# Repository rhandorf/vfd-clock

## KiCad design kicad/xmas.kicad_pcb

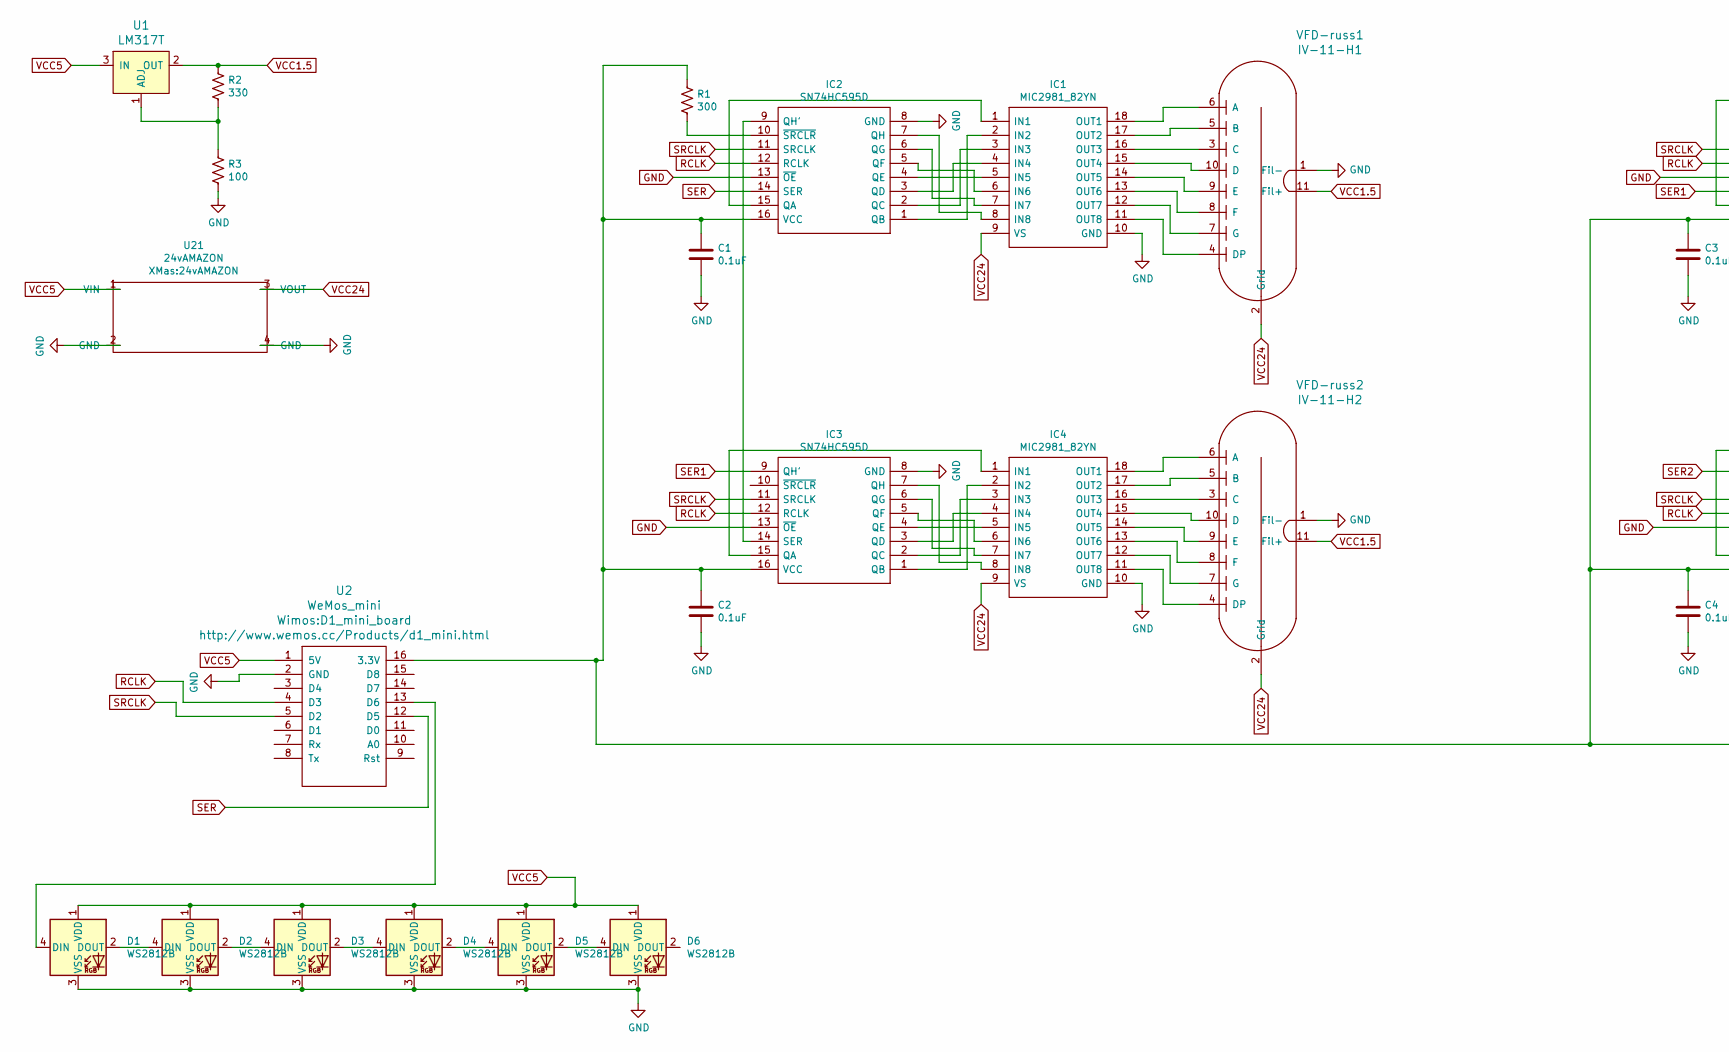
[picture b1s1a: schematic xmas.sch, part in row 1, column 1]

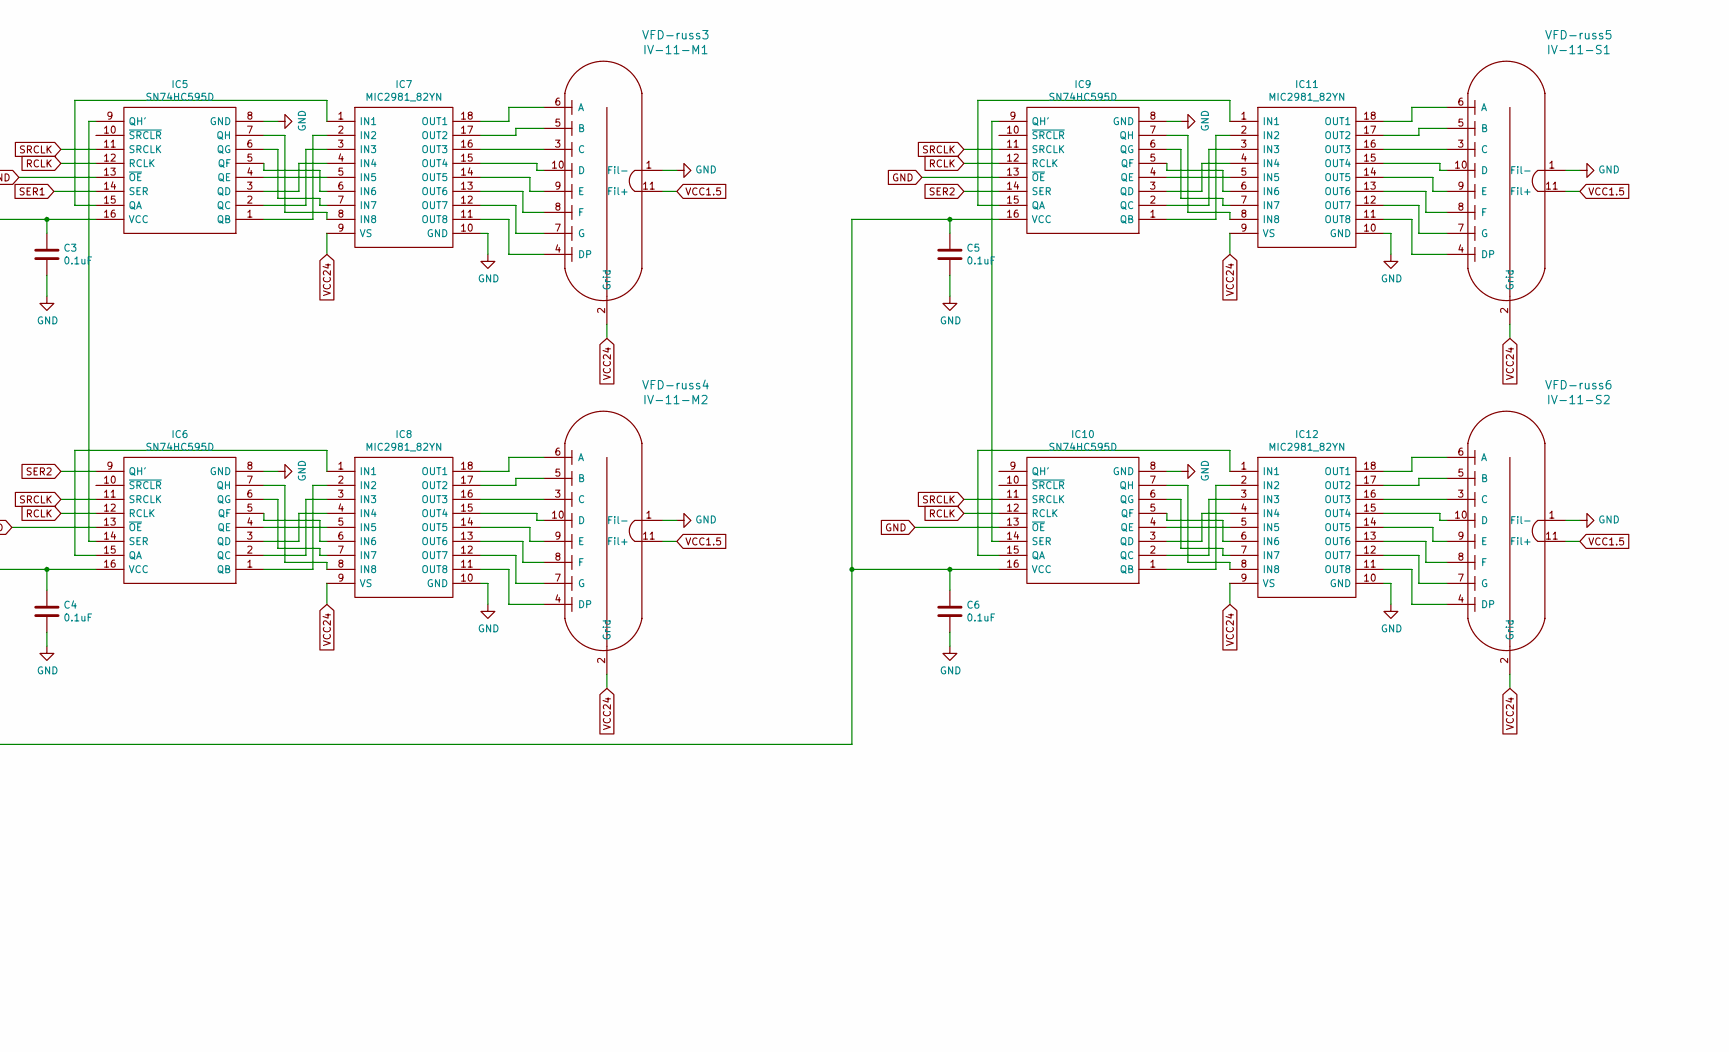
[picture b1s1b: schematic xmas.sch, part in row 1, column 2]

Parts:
C1, C2, C3, C4, C5, C6: 0.1uF; C_1206_3216Metric_Pad1.42x1.75mm_HandSolder
D1, D2, D3, D4, D5, D6: WS2812B; LED_WS2812B_PLCC4_5.0x5.0mm_P3.2mm
IC1, IC4, IC7, IC8, IC11, IC12: MIC2981_82YN; DIP773W53P254L2337H394Q18N; Mouser Part Number 998-MIC2981/82YN
IC2, IC3, IC5, IC6, IC9, IC10: SN74HC595D; SOIC127P600X175-16N; Mouser Part Number 595-SN74HC595D
R1: 300; R_1206_3216Metric_Pad1.42x1.75mm_HandSolder
R2: 330; R_1206_3216Metric_Pad1.42x1.75mm_HandSolder
R3: 100; R_1206_3216Metric_Pad1.42x1.75mm_HandSolder
U1: LM317T; TO-220-3; MPN LM317T; Digi-Key_PN 497-1575-5-ND
U2: WeMos_mini; D1_mini_board
U21: 24vAMAZON
VFD-russ1: IV-11-H1; IV-11
VFD-russ2: IV-11-H2; IV-11
VFD-russ3: IV-11-M1; IV-11
VFD-russ4: IV-11-M2; IV-11
VFD-russ5: IV-11-S1; IV-11
VFD-russ6: IV-11-S2; IV-11

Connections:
GND: C1.2, C2.2, C3.2, C4.2, C5.2, C6.2, D1.3 (VSS), D2.3 (VSS), D3.3 (VSS), D4.3 (VSS), D5.3 (VSS), D6.3 (VSS), IC1.10 (GND), IC2.8 (GND), IC2.13 (~OE), IC3.8 (GND), IC3.13 (~OE), IC4.10 (GND), IC5.8 (GND), IC5.13 (~OE), IC6.8 (GND), IC6.13 (~OE), IC7.10 (GND), IC8.10 (GND), IC9.8 (GND), IC9.13 (~OE), IC10.8 (GND), IC10.13 (~OE), IC11.10 (GND), IC12.10 (GND), R3.2, U2.2 (GND), U21.2 (GND), U21.4 (GND), VFD-russ1.1 (Fil-), VFD-russ2.1 (Fil-), VFD-russ3.1 (Fil-), VFD-russ4.1 (Fil-), VFD-russ5.1 (Fil-), VFD-russ6.1 (Fil-)
unnamed: C1.1, C2.1, C3.1, C4.1, C5.1, C6.1, IC2.16 (VCC), IC3.16 (VCC), IC5.16 (VCC), IC6.16 (VCC), IC9.16 (VCC), IC10.16 (VCC), R1.1, U2.16 (3.3V)
unnamed: D1.2 (DOUT), D2.4 (DIN)
unnamed: D1.4 (DIN), U2.13 (D6)
unnamed: D2.2 (DOUT), D3.4 (DIN)
unnamed: D3.2 (DOUT), D4.4 (DIN)
unnamed: D4.2 (DOUT), D5.4 (DIN)
unnamed: D5.2 (DOUT), D6.4 (DIN)
unnamed: IC1.1 (IN1), IC2.15 (QA)
unnamed: IC1.2 (IN2), IC2.1 (QB)
unnamed: IC1.3 (IN3), IC2.2 (QC)
unnamed: IC1.4 (IN4), IC2.3 (QD)
unnamed: IC1.5 (IN5), IC2.4 (QE)
unnamed: IC1.6 (IN6), IC2.5 (QF)
unnamed: IC1.7 (IN7), IC2.6 (QG)
unnamed: IC1.8 (IN8), IC2.7 (QH)
unnamed: IC1.11 (OUT8), VFD-russ1.4 (DP)
unnamed: IC1.12 (OUT7), VFD-russ1.7 (G)
unnamed: IC1.13 (OUT6), VFD-russ1.8 (F)
unnamed: IC1.14 (OUT5), VFD-russ1.9 (E)
unnamed: IC1.15 (OUT4), VFD-russ1.10 (D)
unnamed: IC1.16 (OUT3), VFD-russ1.3 (C)
unnamed: IC1.17 (OUT2), VFD-russ1.5 (B)
unnamed: IC1.18 (OUT1), VFD-russ1.6 (A)
unnamed: IC2.9 (QH'), IC3.14 (SER)
unnamed: IC2.10 (~SRCLR), R1.2
unnamed: IC3.1 (QB), IC4.2 (IN2)
unnamed: IC3.2 (QC), IC4.3 (IN3)
unnamed: IC3.3 (QD), IC4.4 (IN4)
unnamed: IC3.4 (QE), IC4.5 (IN5)
unnamed: IC3.5 (QF), IC4.6 (IN6)
unnamed: IC3.6 (QG), IC4.7 (IN7)
unnamed: IC3.7 (QH), IC4.8 (IN8)
unnamed: IC3.15 (QA), IC4.1 (IN1)
unnamed: IC4.11 (OUT8), VFD-russ2.4 (DP)
unnamed: IC4.12 (OUT7), VFD-russ2.7 (G)
unnamed: IC4.13 (OUT6), VFD-russ2.8 (F)
unnamed: IC4.14 (OUT5), VFD-russ2.9 (E)
unnamed: IC4.15 (OUT4), VFD-russ2.10 (D)
unnamed: IC4.16 (OUT3), VFD-russ2.3 (C)
unnamed: IC4.17 (OUT2), VFD-russ2.5 (B)
unnamed: IC4.18 (OUT1), VFD-russ2.6 (A)
unnamed: IC5.1 (QB), IC7.2 (IN2)
unnamed: IC5.2 (QC), IC7.3 (IN3)
unnamed: IC5.3 (QD), IC7.4 (IN4)
unnamed: IC5.4 (QE), IC7.5 (IN5)
unnamed: IC5.5 (QF), IC7.6 (IN6)
unnamed: IC5.6 (QG), IC7.7 (IN7)
unnamed: IC5.7 (QH), IC7.8 (IN8)
unnamed: IC5.9 (QH'), IC6.14 (SER)
unnamed: IC5.15 (QA), IC7.1 (IN1)
unnamed: IC6.1 (QB), IC8.2 (IN2)
unnamed: IC6.2 (QC), IC8.3 (IN3)
unnamed: IC6.3 (QD), IC8.4 (IN4)
unnamed: IC6.4 (QE), IC8.5 (IN5)
unnamed: IC6.5 (QF), IC8.6 (IN6)
unnamed: IC6.6 (QG), IC8.7 (IN7)
unnamed: IC6.7 (QH), IC8.8 (IN8)
unnamed: IC6.15 (QA), IC8.1 (IN1)
unnamed: IC7.11 (OUT8), VFD-russ3.4 (DP)
unnamed: IC7.12 (OUT7), VFD-russ3.7 (G)
unnamed: IC7.13 (OUT6), VFD-russ3.8 (F)
unnamed: IC7.14 (OUT5), VFD-russ3.9 (E)
unnamed: IC7.15 (OUT4), VFD-russ3.10 (D)
unnamed: IC7.16 (OUT3), VFD-russ3.3 (C)
unnamed: IC7.17 (OUT2), VFD-russ3.5 (B)
unnamed: IC7.18 (OUT1), VFD-russ3.6 (A)
unnamed: IC8.11 (OUT8), VFD-russ4.4 (DP)
unnamed: IC8.12 (OUT7), VFD-russ4.7 (G)
unnamed: IC8.13 (OUT6), VFD-russ4.8 (F)
unnamed: IC8.14 (OUT5), VFD-russ4.9 (E)
unnamed: IC8.15 (OUT4), VFD-russ4.10 (D)
unnamed: IC8.16 (OUT3), VFD-russ4.3 (C)
unnamed: IC8.17 (OUT2), VFD-russ4.5 (B)
unnamed: IC8.18 (OUT1), VFD-russ4.6 (A)
unnamed: IC10.1 (QB), IC12.2 (IN2)
unnamed: IC10.2 (QC), IC12.3 (IN3)
unnamed: IC10.3 (QD), IC12.4 (IN4)
unnamed: IC10.4 (QE), IC12.5 (IN5)
unnamed: IC10.5 (QF), IC12.6 (IN6)
unnamed: IC10.6 (QG), IC12.7 (IN7)
unnamed: IC10.7 (QH), IC12.8 (IN8)
unnamed: IC9.9 (QH'), IC10.14 (SER)
unnamed: IC10.15 (QA), IC12.1 (IN1)
unnamed: IC9.15 (QA), IC11.1 (IN1)
unnamed: IC9.1 (QB), IC11.2 (IN2)
unnamed: IC9.2 (QC), IC11.3 (IN3)
unnamed: IC9.3 (QD), IC11.4 (IN4)
unnamed: IC9.4 (QE), IC11.5 (IN5)
unnamed: IC9.5 (QF), IC11.6 (IN6)
unnamed: IC9.6 (QG), IC11.7 (IN7)
unnamed: IC9.7 (QH), IC11.8 (IN8)
unnamed: IC11.11 (OUT8), VFD-russ5.4 (DP)
unnamed: IC11.12 (OUT7), VFD-russ5.7 (G)
unnamed: IC11.13 (OUT6), VFD-russ5.8 (F)
unnamed: IC11.14 (OUT5), VFD-russ5.9 (E)
unnamed: IC11.15 (OUT4), VFD-russ5.10 (D)
unnamed: IC11.16 (OUT3), VFD-russ5.3 (C)
unnamed: IC11.17 (OUT2), VFD-russ5.5 (B)
unnamed: IC11.18 (OUT1), VFD-russ5.6 (A)
unnamed: IC12.11 (OUT8), VFD-russ6.4 (DP)
unnamed: IC12.12 (OUT7), VFD-russ6.7 (G)
unnamed: IC12.13 (OUT6), VFD-russ6.8 (F)
unnamed: IC12.14 (OUT5), VFD-russ6.9 (E)
unnamed: IC12.15 (OUT4), VFD-russ6.10 (D)
unnamed: IC12.16 (OUT3), VFD-russ6.3 (C)
unnamed: IC12.17 (OUT2), VFD-russ6.5 (B)
unnamed: IC12.18 (OUT1), VFD-russ6.6 (A)
unnamed: R2.2, R3.1, U1.1 (ADJ)
RCLK: IC2.12 (RCLK), IC3.12 (RCLK), IC5.12 (RCLK), IC6.12 (RCLK), IC9.12 (RCLK), IC10.12 (RCLK), U2.4 (D3)
SER: IC2.14 (SER), U2.12 (D5)
SER1: IC3.9 (QH'), IC5.14 (SER)
SER2: IC6.9 (QH'), IC9.14 (SER)
SRCLK: IC2.11 (SRCLK), IC3.11 (SRCLK), IC5.11 (SRCLK), IC6.11 (SRCLK), IC9.11 (SRCLK), IC10.11 (SRCLK), U2.5 (D2)
VCC1.5: R2.1, U1.2 (OUT), VFD-russ1.11 (Fil+), VFD-russ2.11 (Fil+), VFD-russ3.11 (Fil+), VFD-russ4.11 (Fil+), VFD-russ5.11 (Fil+), VFD-russ6.11 (Fil+)
VCC5: D1.1 (VDD), D2.1 (VDD), D3.1 (VDD), D4.1 (VDD), D5.1 (VDD), D6.1 (VDD), U1.3 (IN), U2.1 (5V), U21.1 (VIN)
VCC24: IC1.9 (VS), IC4.9 (VS), IC7.9 (VS), IC8.9 (VS), IC11.9 (VS), IC12.9 (VS), U21.3 (VOUT), VFD-russ1.2 (Grid), VFD-russ2.2 (Grid), VFD-russ3.2 (Grid), VFD-russ4.2 (Grid), VFD-russ5.2 (Grid), VFD-russ6.2 (Grid)

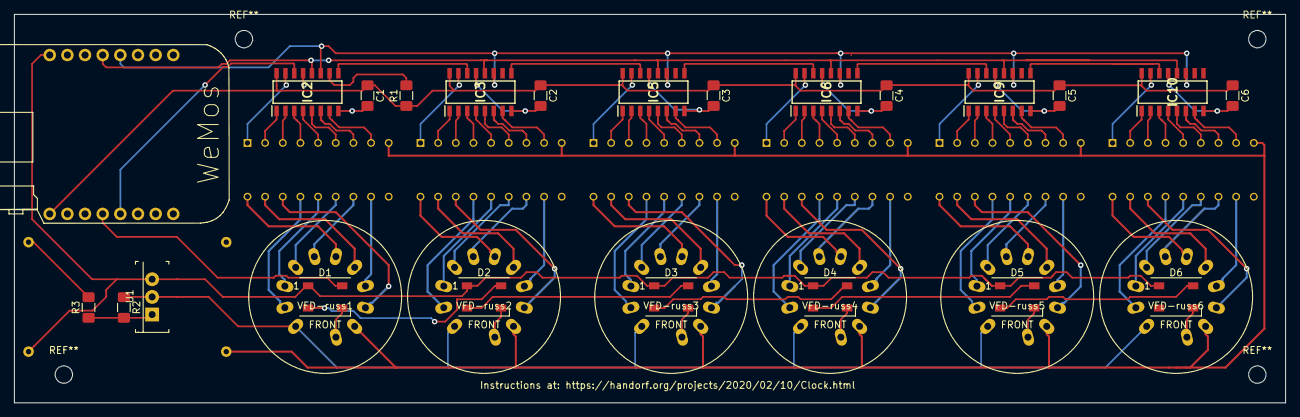
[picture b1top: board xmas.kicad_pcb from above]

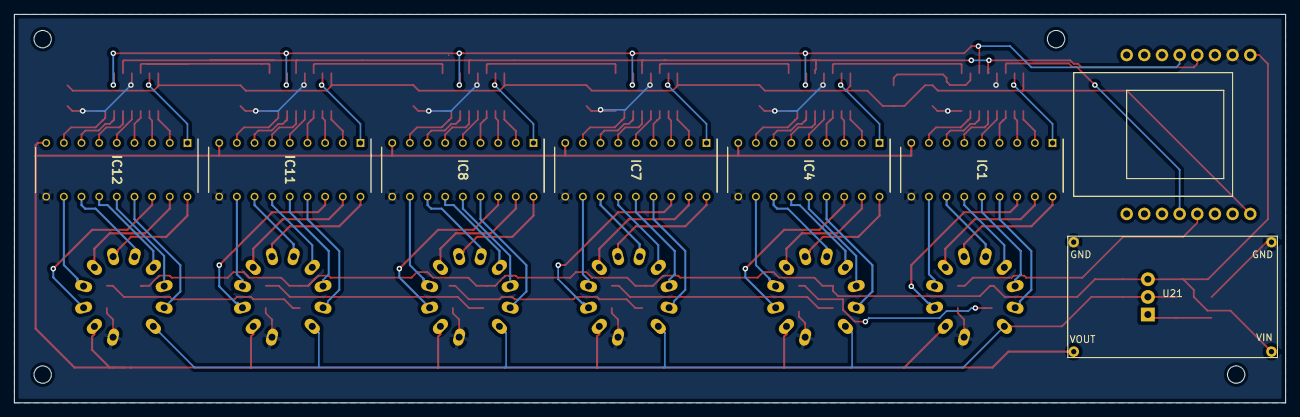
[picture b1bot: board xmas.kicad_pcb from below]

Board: 2 copper layers, 182.9 x 55.9 mm, 36 parts (7 on the bottom side), 117 nets.

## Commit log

2020-02-16 foist
2020-03-26 Rename to make arduino IDE happy, split config into its own file, add config options for animation and color
    Rename to make arduino IDE happy, split config into its own file, add config options for animation and color
2020-03-26 Fix LED change, fix chasing animation change
    Fix LED change, fix chasing animation change
2020-07-01 new wifi
2020-08-18 now with scrolling msg
2021-03-16 new features
